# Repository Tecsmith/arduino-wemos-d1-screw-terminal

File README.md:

# Screw terminal board for Wemos / LOLIN D1 Mini / Mini Pro

| Board | URL |
|---|---|
| [Wemos / LOLIN D1 Mini Screw Terminal Breakout](https://tecsmith.github.io/arduino-wemos-d1-screw-terminal/) |  [`c1k.it/d1m1`](http://c1k.it/d1m1) |

## Help, About, *etc.*

Refer to the [docs folder](docs/index.md).

<p align="center" style="color:#069">★</p>

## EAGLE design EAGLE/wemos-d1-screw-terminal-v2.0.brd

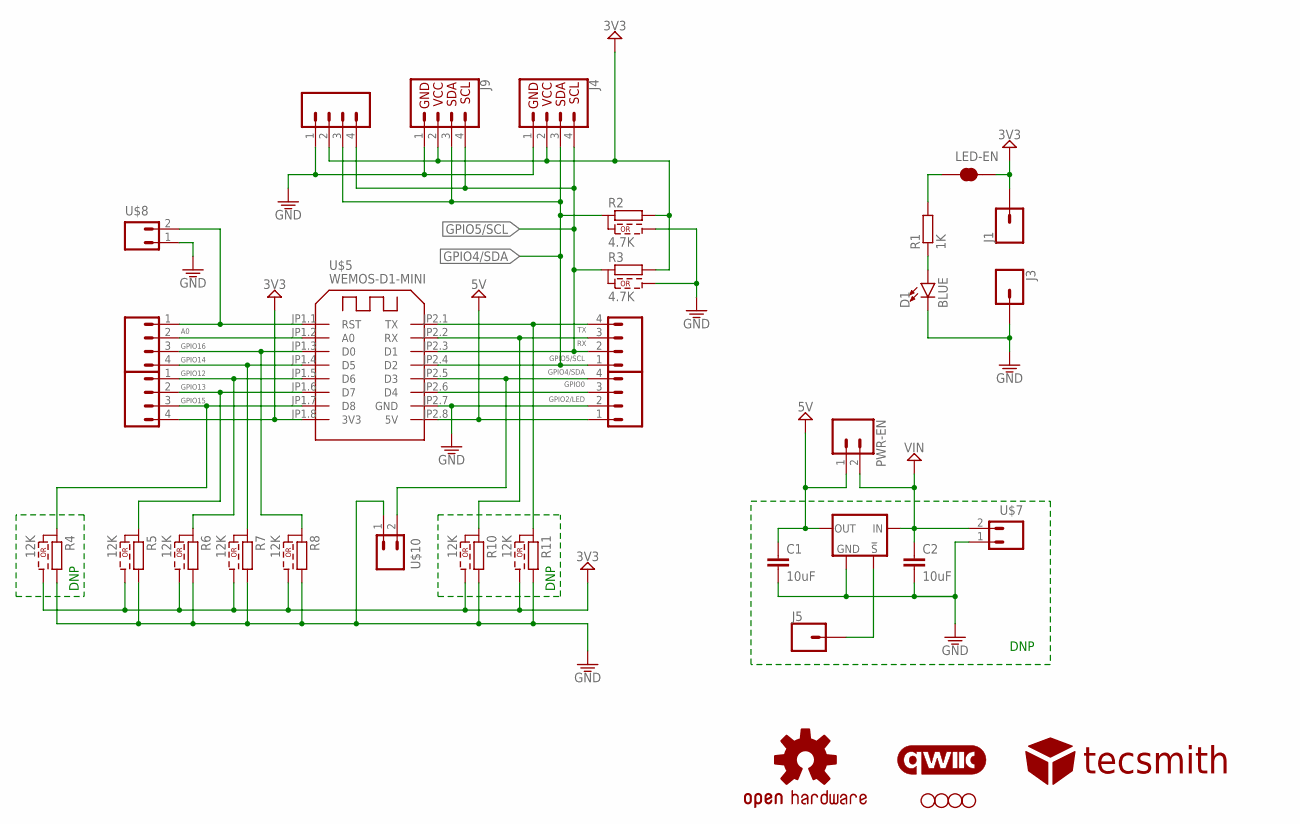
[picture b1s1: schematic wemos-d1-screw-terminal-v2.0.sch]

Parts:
C1, C2: 10uF; 0805
D1: BLUE; LED-0603
H1, H2, H5, H6: STAND-OFF
J1, J3, J5: CONN_01PTH_NO_SILK_YES_STOP; 1X01_NO_SILK
J2: CONN_04PTH; 1X04
J4, J9: QWIIC_RIGHT_ANGLE; JST04_1MM_RA
LED-EN: JUMPER-SMT_2_NC_TRACE_SILK; SMT-JUMPER_2_NC_TRACE_SILK
LOGO1: OSHW-LOGOS; OSHW-LOGO-S
LOGO2: QWIIC_LOGO_6MM; QWIIC_6MM
PWR-EN: CONN_021X02_NO_SILK; 1X02_NO_SILK
R1: 1K; R0603
R2, R3: 4.7K; R0603_JMP
R4, R5, R6, R7, R8, R10, R11: 12K; R0603_JMP
U$1, U$2, U$3, U$4: CON_04SCREW; WURTH_2431_3.5MM_4X_SCREW
U$5: WEMOS-D1-MINI
U$6: POLOLU-VREG; TO-220+1
U$7: CON_02SCREW; WURTH_2431_3.5MM_2X_SCREW
U$8, U$10: JST-PH-2; JST-PH2
U$9: TECSMITH-LOGO

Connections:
A0: U$1.2, U$5.JP1.2 (A0)
GND: C1.2, C2.2, D1.C, J2.1, J3.1, J4.1, J9.1, R2.3, R3.3, R4.2, R5.2, R6.2, R7.2, R8.2, R10.2, R11.2, U$3.2, U$5.JP2.7 (GND), U$6.GND, U$7.1, U$8.1, U$10.1
GPIO0: U$3.4, U$5.JP2.5 (D3), U$10.2
GPIO2/LED: U$3.3, U$5.JP2.6 (D4)
GPIO4/SDA: J2.3, J4.3, J9.3, R2.1, U$4.1, U$5.JP2.4 (D2)
GPIO5/SCL: J2.4, J4.4, J9.4, R3.1, U$4.2, U$5.JP2.3 (D1)
GPIO12: R6.1, U$2.1, U$5.JP1.5 (D6)
GPIO13: R5.1, U$2.2, U$5.JP1.6 (D7)
GPIO14: R7.1, U$1.4, U$5.JP1.4 (D5)
GPIO15: R4.1, U$2.3, U$5.JP1.7 (D8)
GPIO16: R8.1, U$1.3, U$5.JP1.3 (D0)
unnamed: D1.A, R1.1
unnamed: LED-EN.1, R1.2
unnamed: J5.1, U$6.!SHDN
RST: U$1.1, U$5.JP1.1 (RST), U$8.2
RX: R10.1, U$4.3, U$5.JP2.2 (RX)
TX: R11.1, U$4.4, U$5.JP2.1 (TX)
VCC: J1.1, J2.2, J4.2, J9.2, LED-EN.2, R2.2, R3.2, R4.3, R5.3, R6.3, R7.3, R8.3, R10.3, R11.3, U$2.4, U$5.JP1.8 (3V3)
VCC_1: C1.1, PWR-EN.1, U$3.1, U$5.JP2.8 (5V), U$6.OUT
VCC_2: C2.1, PWR-EN.2, U$6.IN, U$7.2

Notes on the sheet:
DNP

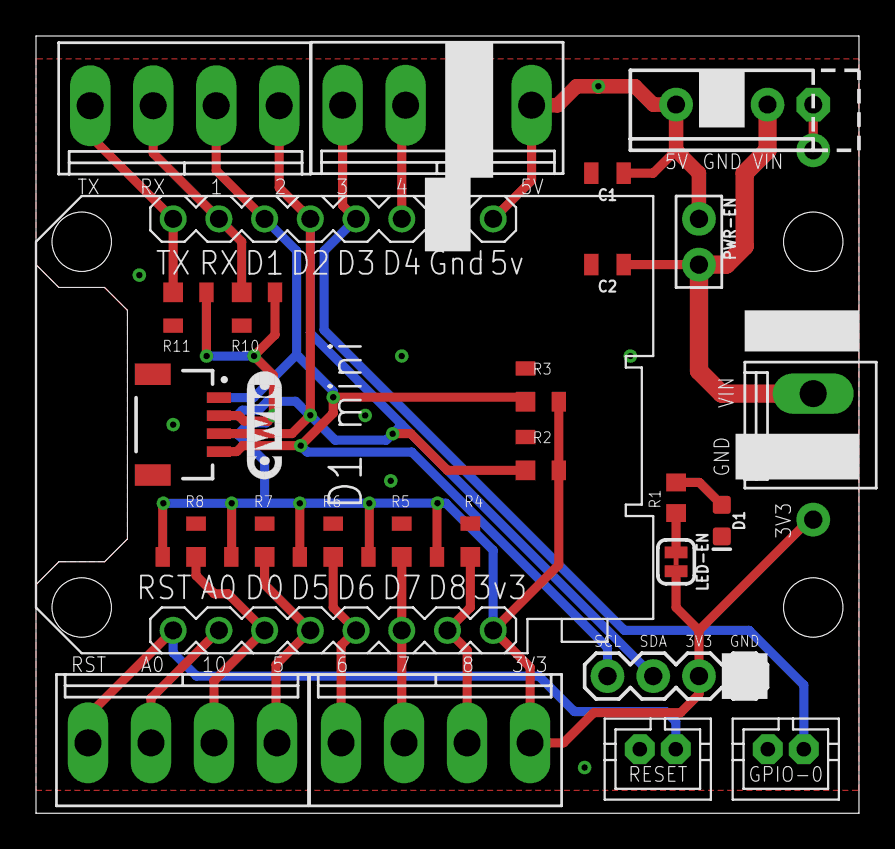
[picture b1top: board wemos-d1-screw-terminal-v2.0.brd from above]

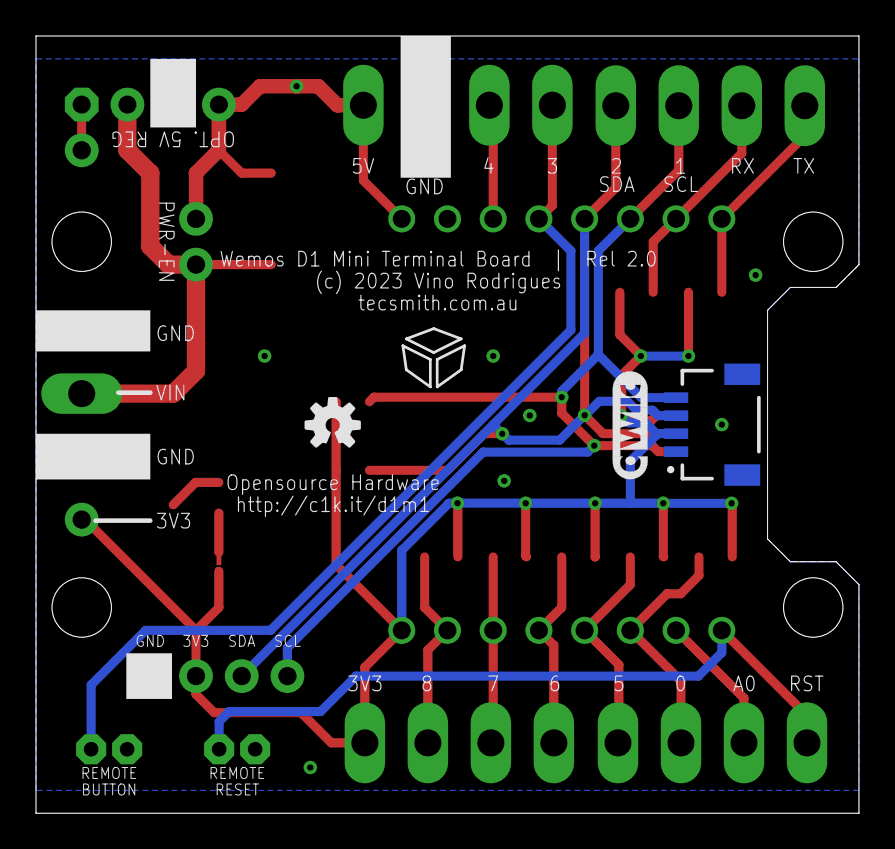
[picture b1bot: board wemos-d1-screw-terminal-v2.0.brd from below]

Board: 2 copper layers, 45.7 x 43.2 mm, 38 parts (4 on the bottom side), 20 nets.

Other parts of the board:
LOGO3: QWIIC_LOGO_6MM; QWIIC_6MM

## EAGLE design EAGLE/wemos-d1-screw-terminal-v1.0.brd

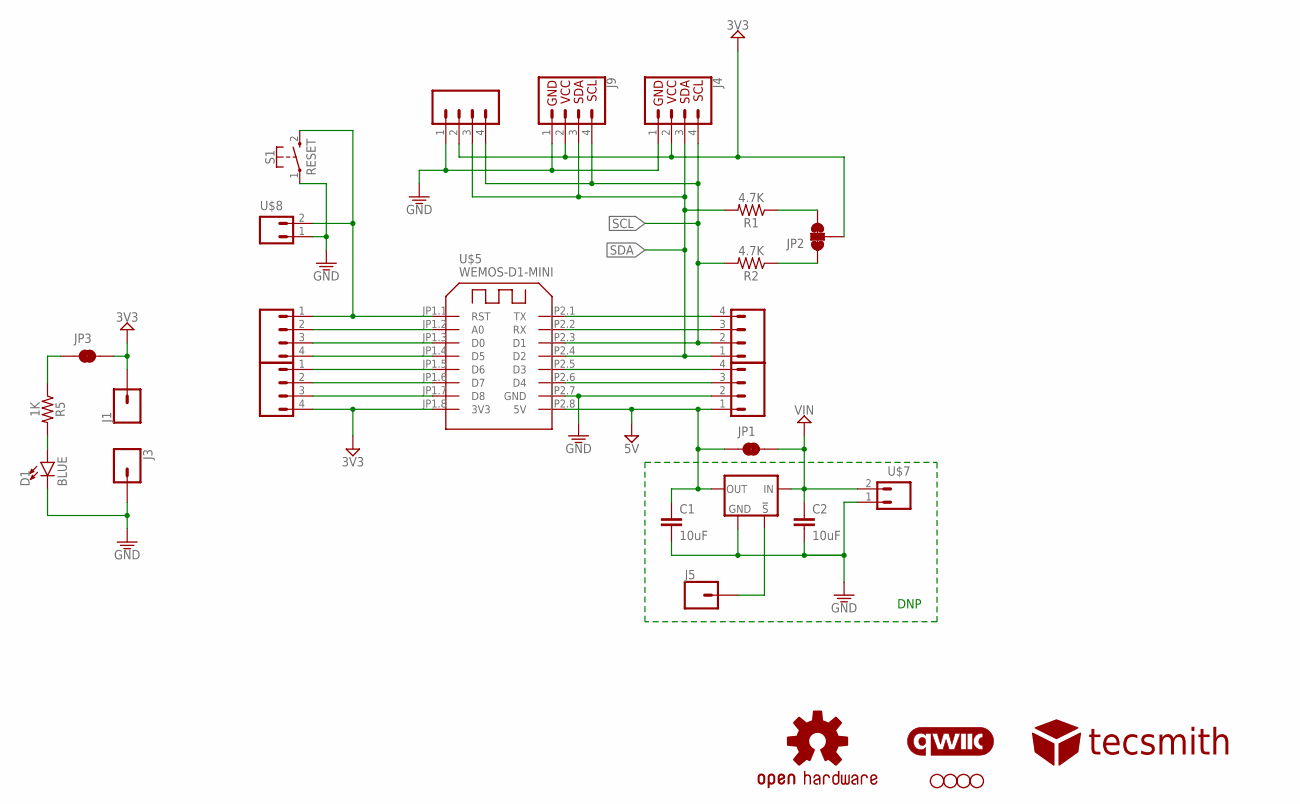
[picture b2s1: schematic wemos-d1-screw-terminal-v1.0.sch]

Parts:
C1, C2: 10uF; 0805
D1: BLUE; LED-0603
H1, H2, H5, H6: STAND-OFF
J1, J3, J5: CONN_01PTH_NO_SILK_YES_STOP; 1X01_NO_SILK
J2: CONN_04PTH; 1X04
J4, J9: QWIIC_RIGHT_ANGLE; JST04_1MM_RA
JP1: JUMPER-COMBO_2_NC_TRACE; COMBO-JUMPER_2_NC_TRACE
JP2: JUMPER-SMT_3_2-NC_TRACE_SILK; SMT-JUMPER_3_2-NC_TRACE_SILK
JP3: JUMPER-SMT_2_NC_TRACE_SILK; SMT-JUMPER_2_NC_TRACE_SILK
LOGO1: OSHW-LOGOS; OSHW-LOGO-S
LOGO2: QWIIC_LOGO_6MM; QWIIC_6MM
R1, R2: 4.7K; 0805
R5: 1K; 0603
S1: RESET; SKRKAEE020
U$1, U$2, U$3, U$4: CON_04SCREW; WURTH_2431_3.5MM_4X_SCREW
U$5: WEMOS-D1-MINI
U$6: POLOLU-VREG; TO-220+1
U$7: CON_02SCREW; WURTH_2431_3.5MM_2X_SCREW
U$8: JST-PH-2; JST-PH2
U$9: TECSMITH-LOGO

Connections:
GND: C1.2, C2.2, D1.C, J2.1, J3.1, J4.1, J9.1, S1.1, U$3.2, U$5.JP2.7 (GND), U$6.GND, U$7.1, U$8.1
unnamed: S1.2 (3), U$1.1, U$5.JP1.1 (RST), U$8.2
unnamed: U$1.2, U$5.JP1.2 (A0)
unnamed: U$1.3, U$5.JP1.3 (D0)
unnamed: U$1.4, U$5.JP1.4 (D5)
unnamed: U$2.1, U$5.JP1.5 (D6)
unnamed: D1.A, R5.2
unnamed: U$2.2, U$5.JP1.6 (D7)
unnamed: U$2.3, U$5.JP1.7 (D8)
unnamed: JP3.1, R5.1
unnamed: U$4.4, U$5.JP2.1 (TX)
unnamed: U$4.3, U$5.JP2.2 (RX)
unnamed: J5.1, U$6.!SHDN
unnamed: U$3.4, U$5.JP2.5 (D3)
unnamed: U$3.3, U$5.JP2.6 (D4)
unnamed: JP2.1, R2.1
unnamed: JP2.3, R1.1
SCL: J2.4, J4.4, J9.4, R2.2, U$4.2, U$5.JP2.3 (D1)
SDA: J2.3, J4.3, J9.3, R1.2, U$4.1, U$5.JP2.4 (D2)
VCC: J1.1, J2.2, J4.2, J9.2, JP2.2, JP3.2, U$2.4, U$5.JP1.8 (3V3)
VCC_1: C1.1, JP1.1, JP1.3 (1), U$3.1, U$5.JP2.8 (5V), U$6.OUT
VCC_2: C2.1, JP1.2, JP1.4 (2), U$6.IN, U$7.2

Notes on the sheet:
DNP

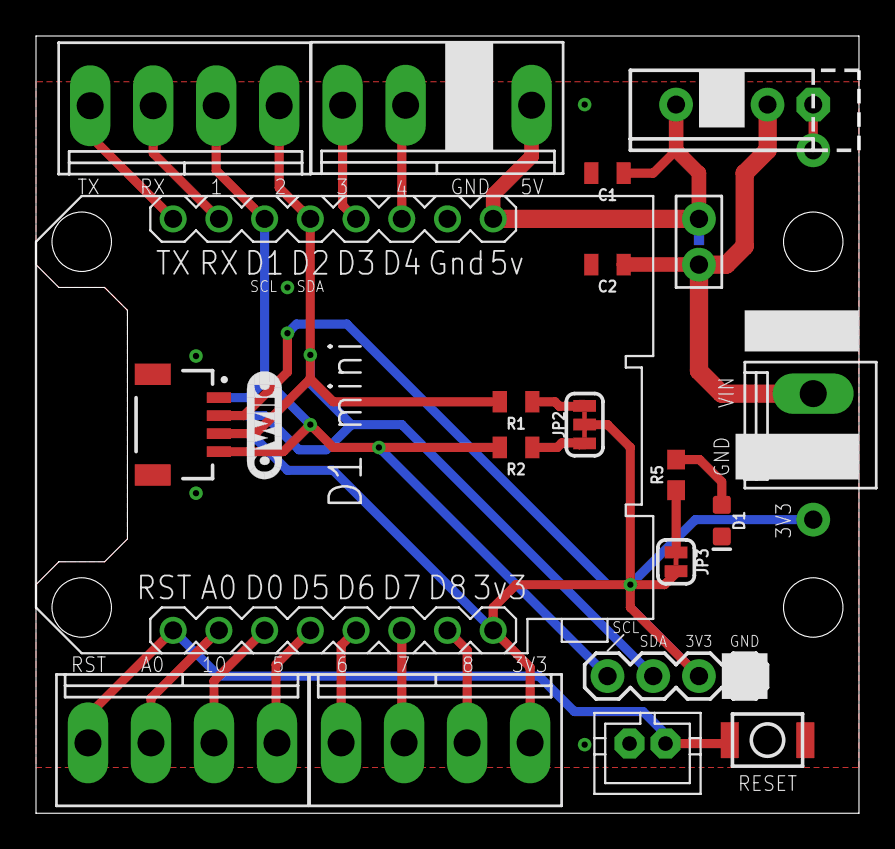
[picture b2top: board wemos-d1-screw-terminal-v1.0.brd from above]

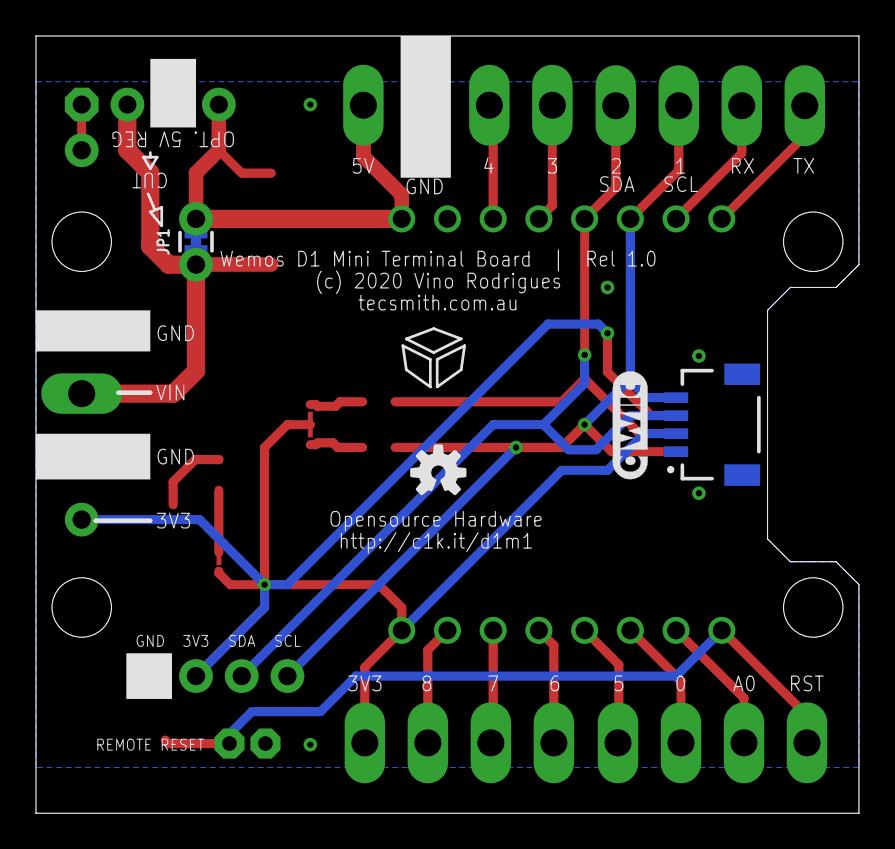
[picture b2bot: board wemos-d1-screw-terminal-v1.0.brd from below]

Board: 2 copper layers, 45.7 x 43.2 mm, 32 parts (5 on the bottom side), 22 nets.

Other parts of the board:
LOGO3: QWIIC_LOGO_6MM; QWIIC_6MM

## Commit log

2021-07-04 moved from fan-control project
2021-07-05 move items from arduino-fan-control-v2 project

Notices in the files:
EAGLE/wemos-d1-screw-terminal-v1.0.brd:
(c) 2020 Vino Rodrigues
EAGLE/wemos-d1-screw-terminal-v2.0.brd:
(c) 2023 Vino Rodrigues
parts and their libraries:
SparkFun-Connectors: Licensing: Creative Commons ShareAlike 4.0 International - https://creativecommons.org/licenses/by-sa/4.0
